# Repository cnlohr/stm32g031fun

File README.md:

# stm32g031fun
CNLohr's forray into the stm32g031

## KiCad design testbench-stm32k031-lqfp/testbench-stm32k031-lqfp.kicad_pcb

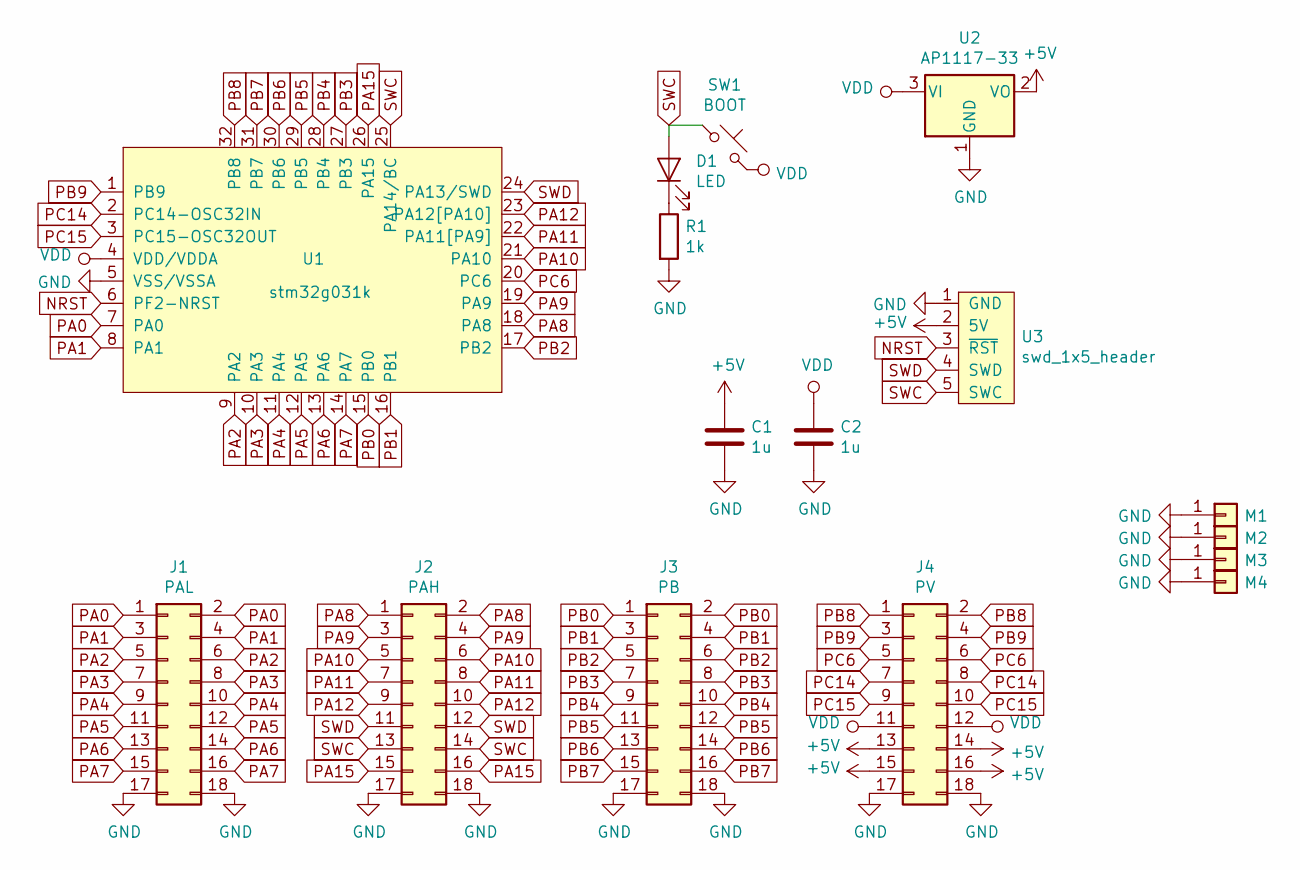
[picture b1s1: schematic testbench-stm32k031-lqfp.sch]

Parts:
C1, C2: 1u; C_0603_1608Metric
D1: LED; LED_0603_1608Metric
J1: PAL; PinHeader_2x09_P2.54mm_Vertical_SMD
J2: PAH; PinHeader_2x09_P2.54mm_Vertical_SMD
J3: PB; PinHeader_2x09_P2.54mm_Vertical_SMD
J4: PV; PinHeader_2x09_P2.54mm_Vertical_SMD
M1, M2, M3, M4: MountingHole_3.2mm_M3_DIN965_Pad
R1: 1k; R_0603_1608Metric
SW1: BOOT; SW_SPST_EVPBF
U1: stm32g031k; LQFP-32_7x7mm_P0.8mm
U2: AP1117-33; SOT-23
U3: swd_1x5_header; POGO-5-SWD

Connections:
+5V: C1.1, J4.13, J4.14, J4.15, J4.16, U2.2 (VO), U3.2 (5V)
GND: C1.2, C2.2, J1.17, J1.18, J2.17, J2.18, J3.17, J3.18, J4.17, J4.18, M1.1, M2.1, M3.1, M4.1, R1.2, U1.5 (VSS/VSSA), U2.1 (GND), U3.1 (GND)
NRST: U1.6 (PF2-NRST), U3.3 (~RST~)
unnamed: D1.1 (K), R1.1
PA0: J1.1, J1.2, U1.7 (PA0)
PA1: J1.3, J1.4, U1.8 (PA1)
PA2: J1.5, J1.6, U1.9 (PA2)
PA3: J1.7, J1.8, U1.10 (PA3)
PA4: J1.9, J1.10, U1.11 (PA4)
PA5: J1.11, J1.12, U1.12 (PA5)
PA6: J1.13, J1.14, U1.13 (PA6)
PA7: J1.15, J1.16, U1.14 (PA7)
PA8: J2.1, J2.2, U1.18 (PA8)
PA9: J2.3, J2.4, U1.19 (PA9)
PA10: J2.5, J2.6, U1.21 (PA10)
PA11: J2.7, J2.8, U1.22 (PA11[PA9])
PA12: J2.9, J2.10, U1.23 (PA12[PA10])
PA15: J2.15, J2.16, U1.26 (PA15)
PB0: J3.1, J3.2, U1.15 (PB0)
PB1: J3.3, J3.4, U1.16 (PB1)
PB2: J3.5, J3.6, U1.17 (PB2)
PB3: J3.7, J3.8, U1.27 (PB3)
PB4: J3.9, J3.10, U1.28 (PB4)
PB5: J3.11, J3.12, U1.29 (PB5)
PB6: J3.13, J3.14, U1.30 (PB6)
PB7: J3.15, J3.16, U1.31 (PB7)
PB8: J4.1, J4.2, U1.32 (PB8)
PB9: J4.3, J4.4, U1.1 (PB9)
PC6: J4.5, J4.6, U1.20 (PC6)
PC14: J4.7, J4.8, U1.2 (PC14-OSC32IN)
PC15: J4.9, J4.10, U1.3 (PC15-OSC32OUT)
SWC: D1.2 (A), J2.13, J2.14, SW1.1, U1.25 (PA14/BC), U3.5 (SWC)
SWD: J2.11, J2.12, U1.24 (PA13/SWD), U3.4 (SWD)
VDD: C2.1, J4.11, J4.12, SW1.2, U1.4 (VDD/VDDA), U2.3 (VI)

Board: 2 copper layers, 16 parts (0 on the bottom side), 34 nets, no tracks yet.

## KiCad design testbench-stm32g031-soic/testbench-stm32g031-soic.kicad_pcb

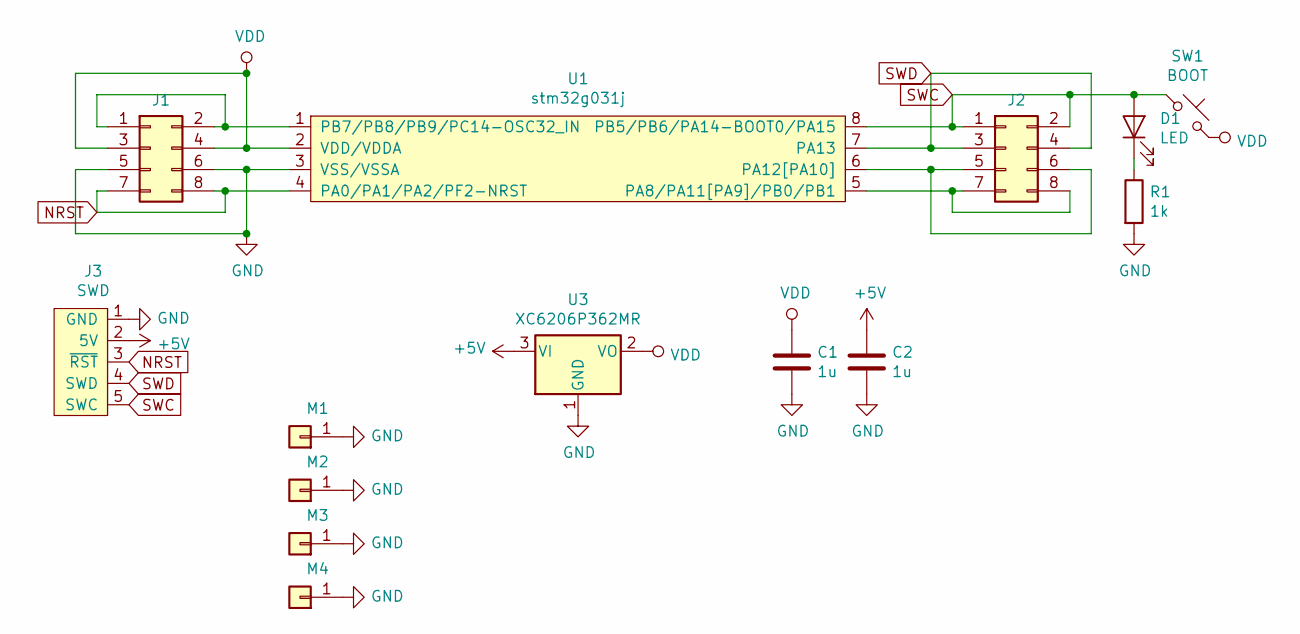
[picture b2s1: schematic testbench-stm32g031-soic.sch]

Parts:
C1, C2: 1u; C_0603_1608Metric
D1: LED; LED_0603_1608Metric
J1, J2: PinSocket_2x04_P2.54mm_Vertical_SMD
J3: SWD; POGO-5-SWD
M1, M2, M3, M4: MountingHole_3.2mm_M3_DIN965_Pad
R1: 1k; R_0603_1608Metric
SW1: BOOT; SW_SPST_EVPBF
U1: stm32g031j; SOIC-8_3.9x4.9mm_P1.27mm
U3: XC6206P362MR; SOT-23

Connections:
+5V: C2.1, J3.2 (5V), U3.3 (VI)
GND: C1.2, C2.2, J1.5, J1.6, J3.1 (GND), M1.1, M2.1, M3.1, M4.1, R1.2, U1.3 (VSS/VSSA), U3.1 (GND)
NRST: J1.7, J1.8, J3.3 (~RST~), U1.4 (PA0/PA1/PA2/PF2-NRST)
unnamed: D1.1 (K), R1.1
unnamed: J1.1, J1.2, U1.1 (PB7/PB8/PB9/PC14-OSC32_IN)
unnamed: J2.5, J2.6, U1.6 (PA12[PA10])
unnamed: J2.7, J2.8, U1.5 (PA8/PA11[PA9]/PB0/PB1)
SWC: D1.2 (A), J2.1, J2.2, J3.5 (SWC), SW1.1, U1.8 (PB5/PB6/PA14-BOOT0/PA15)
SWD: J2.3, J2.4, J3.4 (SWD), U1.7 (PA13)
VDD: C1.1, J1.3, J1.4, SW1.2, U1.2 (VDD/VDDA), U3.2 (VO)

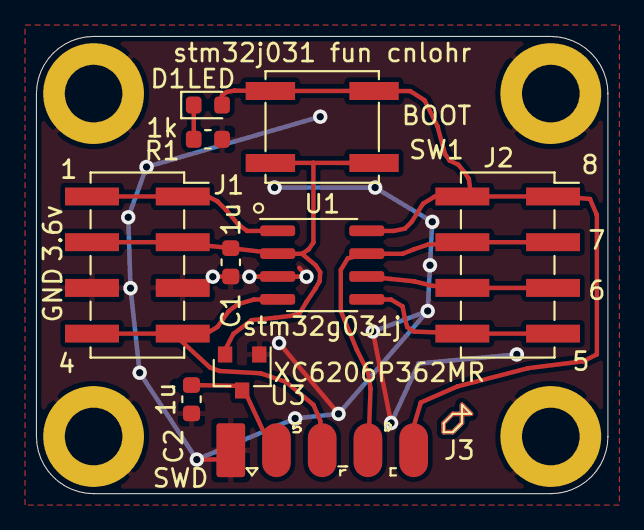
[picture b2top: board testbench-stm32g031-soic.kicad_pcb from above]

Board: 2 copper layers, 31.8 x 25.4 mm, 14 parts (0 on the bottom side), 10 nets.

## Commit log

2020-10-06 first crack
2020-10-07 bumpdesign
